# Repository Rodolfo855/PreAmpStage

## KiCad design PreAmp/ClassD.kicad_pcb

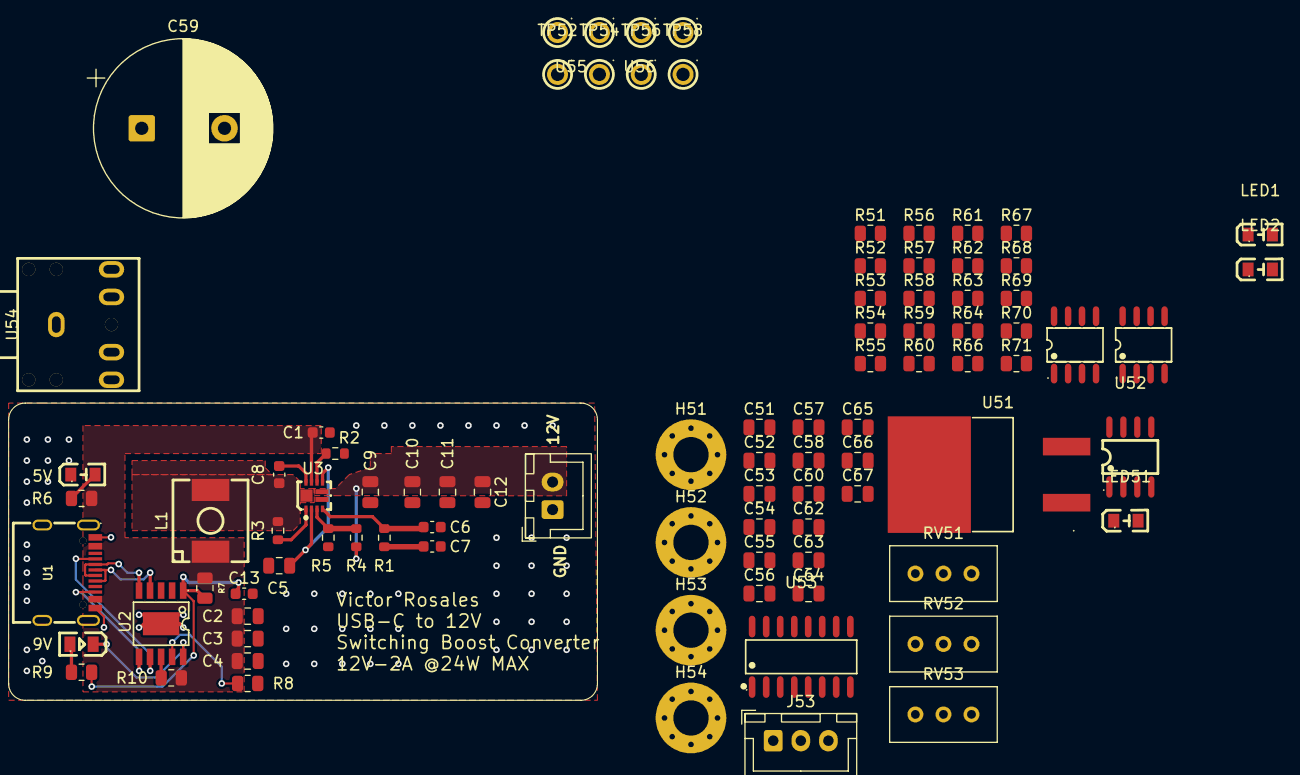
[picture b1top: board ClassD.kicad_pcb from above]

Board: 2 copper layers, 91 parts (0 on the bottom side), 48 nets.

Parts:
5V: LED; C84256_LED0805-RD
9V: 0805; C2297_LED0805-R-RD
C1, C8: 100nF 0603; C_0603_1608Metric
C2, C3, C4: 22uF 0805; C_0805_2012Metric
C5: 10uF 0805; C_0805_2012Metric
C6: 33pF 0603; C_0603_1608Metric
C7: 820pF 0603; C_0603_1608Metric
C9, C10, C11, C12: 22uF-0805; C_0805_2012Metric
C13: 100nF; C_0603_1608Metric
C51, C52, C56, C67: 1uF; C_0805_2012Metric
C53, C66: 10nF; C_0805_2012Metric
C54, C60, C62, C63, C64, C65: 100nF; C_0805_2012Metric
C55: 10uF; C_0805_2012Metric
C57: 680pF; C_0805_2012Metric
C58: 1nF; C_0805_2012Metric
C59: 100uF; CP_Radial_D16.0mm_P7.50mm
H51, H52, H53, H54: MountingHole; MountingHole_3.2mm_M3_Pad_Via
J1: Conn_01x02_Pin; JST_XH_B2B-XH-A_1x02_P2.50mm_Vertical
J53: Conn_01x03; JST_XH_B3B-XH-A_1x03_P2.50mm_Vertical
L1: SPM6530T-4R7M; C76857_IND-SMD_L7_1-W6_5
LED1, LED51: LED; C84256_LED0805-RD
LED2: 0805; C84256_LED0805-RD
R1: 44.2k 0603; R_0603_1608Metric
R2: 110k- 0603; R_0603_1608Metric
R3: 301k-0603; R_0603_1608Metric
R4: 1.05M 0603; R_0603_1608Metric
R5: 118k 0603; R_0603_1608Metric
R6: 4.7k-0805; R_0805_2012Metric
R7: 1k-0805; R_0805_2012Metric
R8: 6.8k-0805; R_0805_2012Metric
R9: 3.3k-0805; R_0805_2012Metric
R10: 10k-0805; R_0805_2012Metric
R51: 470k; R_0805_2012Metric
R52, R53, R55, R57, R58, R67, R71: 10k; R_0805_2012Metric
R54: 56k; R_0805_2012Metric
R56, R59, R61, R62, R63, R64: 1k; R_0805_2012Metric
R60: 3.3k; R_0805_2012Metric
R66: 24k; R_0805_2012Metric
R68: 820R; R_0805_2012Metric
R69: 680R; R_0805_2012Metric
R70: 100k; R_0805_2012Metric
RV51: 100k; Potentiometer_Bourns_3296W_Vertical
RV52, RV53: 10k; Potentiometer_Bourns_3296W_Vertical
TP51, TP52, TP53, TP54, TP55, TP56, TP57, TP58: TestPoint; C5277086_TEST-TH_BD2_54-P1_4_RED
U1: GT-USB-7010ASV; C2988369_USB-C-SMD_G-SWITCH_GT-USB-7010ASV
U2: CH224K; C970725_ESSOP-10_L4_9-W3_9-P1_0-LS6_0-TL-EP
U3: TPS61089RNRR; C165129_VQFN-HR_L2_5-W2_0-P0_50-TL-EP
U51: L7809ABD2T-TR; C262905_D2PAK_L10_0-W9_0-P2_54-LS15_0-BR
U52: OPA1678; C1850241_SOIC-8_L5_0-W4_0-P1_27-LS6_0-BL
U53: TL594; C157346_SOIC-16_L9_9-W3_9-P1_27-LS6_0-BL
U54: SJ1-3525NG; C4991936_AUDIO-TH_SJ1-3525NG
U55: LM393BIDR; C2865059_SOIC-8_L4_9-W3_9-P1_27-LS6_0-BL
U56: TLC555IDR; C6987_SOIC-8_L4_9-W3_9-P1_27-LS6_0-BL

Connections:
!PWM: J53.3, R62.1, TP55.1, U53.10 (E2)
+9V: C53.1, C54.1, C62.1, C63.1, C64.1, C65.1, R54.1, R66.1, R70.1, R71.1, TP53.1, U51.3 (OUTPUT), U52.8 (V+), U55.8 (VCC), U56.4 (RESET), U56.8 (VDD)
+12V: C9.1, C10.1, C11.1, C12.1, C51.1, C59.1, C60.1, J1.2, R4.1, R61.1, TP54.1, U3.6 (VOUT), U51.1 (INPUT), U53.11 (C2), U53.12 (VCC)
AUDIO: C57.2, R57.2, R59.1, TP57.1, U52.7, U53.1 (1IN+), U55.2 (1IN-), U55.5 (2IN+)
CC1: U1.A5 (CC1), U2.7 (CC1)
CC2: U1.B5 (CC2), U2.6 (CC2)
DM: U1.A7 (DN1), U1.B7 (DN2), U2.5 (DM)
DP: U1.A6 (DP1), U1.B6 (DP2), U2.4 (DP)
FB: U53.2 (1IN-), U53.3 (FB)
GND: 5V.1 (-), C1.2, C2.2, C3.2, C4.2, C5.2, C6.2, C7.2, C9.2, C10.2, C11.2, C12.2, C13.2, C51.2, C53.2, C54.2, C55.2, C58.2, C59.2, C60.2, C62.2, C63.2, C64.2, C65.2, C66.2, C67.2, J1.1, J53.2, LED1.1 (-), LED51.1 (-), R2.2, R5.2, R8.1, R51.1, R56.2, R58.2, R59.2, R60.2, R62.2, R68.2, TP52.1, U1.A1B12 (GND), U1.B1A12 (GND), U2.11 (GND), U3.5 (GND), U51.2 (GND), U52.4 (V-), U53.4 (DTC), U53.7 (GND), U53.9 (E1), U53.13 (OUTCTRL), U53.16 (2IN+), U54.1 (GND(MIC)), U54.4 (LET), U54.5 (DETECT), U55.4 (GND), U56.1 (GND)
unnamed: C7.1, R1.2
unnamed: C52.1, R52.1
unnamed: C52.2, R51.2, R63.2, R64.2
unnamed: C56.1, R55.2
unnamed: 5V.2 (+), LED1.2 (+), R6.1
unnamed: 9V.1 (A), LED2.1 (A), R9.2
unnamed: 9V.2 (K), LED2.2 (K), U2.10 (PG)
unnamed: LED51.2 (+), R69.2
unnamed: R53.2, RV51.1
unnamed: R55.1, R56.1, RV51.2, RV51.3, U52.1
unnamed: R58.1, RV52.1
unnamed: R60.1, RV53.3
unnamed: R8.2, U2.9 (CFG1)
unnamed: R10.1, U2.8 (VBUS)
unnamed: C8.2, U3.10 (BOOT)
unnamed: C6.1, R1.1, U3.4 (COMP)
unnamed: C5.1, U3.2 (VCC), U3.7 (EN)
unnamed: R4.2, R5.1, U3.3 (FB)
unnamed: R3.2, U3.1 (FSW)
unnamed: R2.1, U3.8 (ILIM)
unnamed: C8.1, L1.2, R3.1, U3.11 (SW)
unnamed: R52.2, R53.1, U52.2 (-)
unnamed: C56.2, C57.1, R57.1, U52.6 (-)
unnamed: U53.14 (REF), U53.15 (2IN-)
unnamed: RV53.1, RV53.2, U53.6 (RT)
unnamed: R64.1, U54.2 (MIC(GND))
unnamed: R63.1, U54.3 (RT)
unnamed: R71.2, U55.1 (1OUT), U55.7 (2OUT), U56.2 (TRIG)
unnamed: C66.1, U56.5 (CONT)
unnamed: C67.1, R70.2, U56.6 (THRES), U56.7 (DISCH)
unnamed: R69.1, U56.3 (OUT)
PWM: J53.1, R61.2, TP56.1, U53.8 (C1)
SAWTOOTH: C58.1, TP58.1, U53.5 (CT)
VBUS: C1.1, C2.1, C3.1, C4.1, L1.1, R6.2, R7.2, R10.2, U1.A4B9 (VBUS), U1.B4A9 (VBUS), U3.9 (VIN)
VDC: C55.1, R54.2, RV52.2, RV52.3, TP51.1, U52.3 (+), U52.5 (+)
VDD: C13.1, R7.1, R9.1, U2.1 (VDD)
VREFHIGH: R66.2, R67.1, U55.3 (1IN+)
VREFLOW: R67.2, R68.1, U55.6 (2IN-)
